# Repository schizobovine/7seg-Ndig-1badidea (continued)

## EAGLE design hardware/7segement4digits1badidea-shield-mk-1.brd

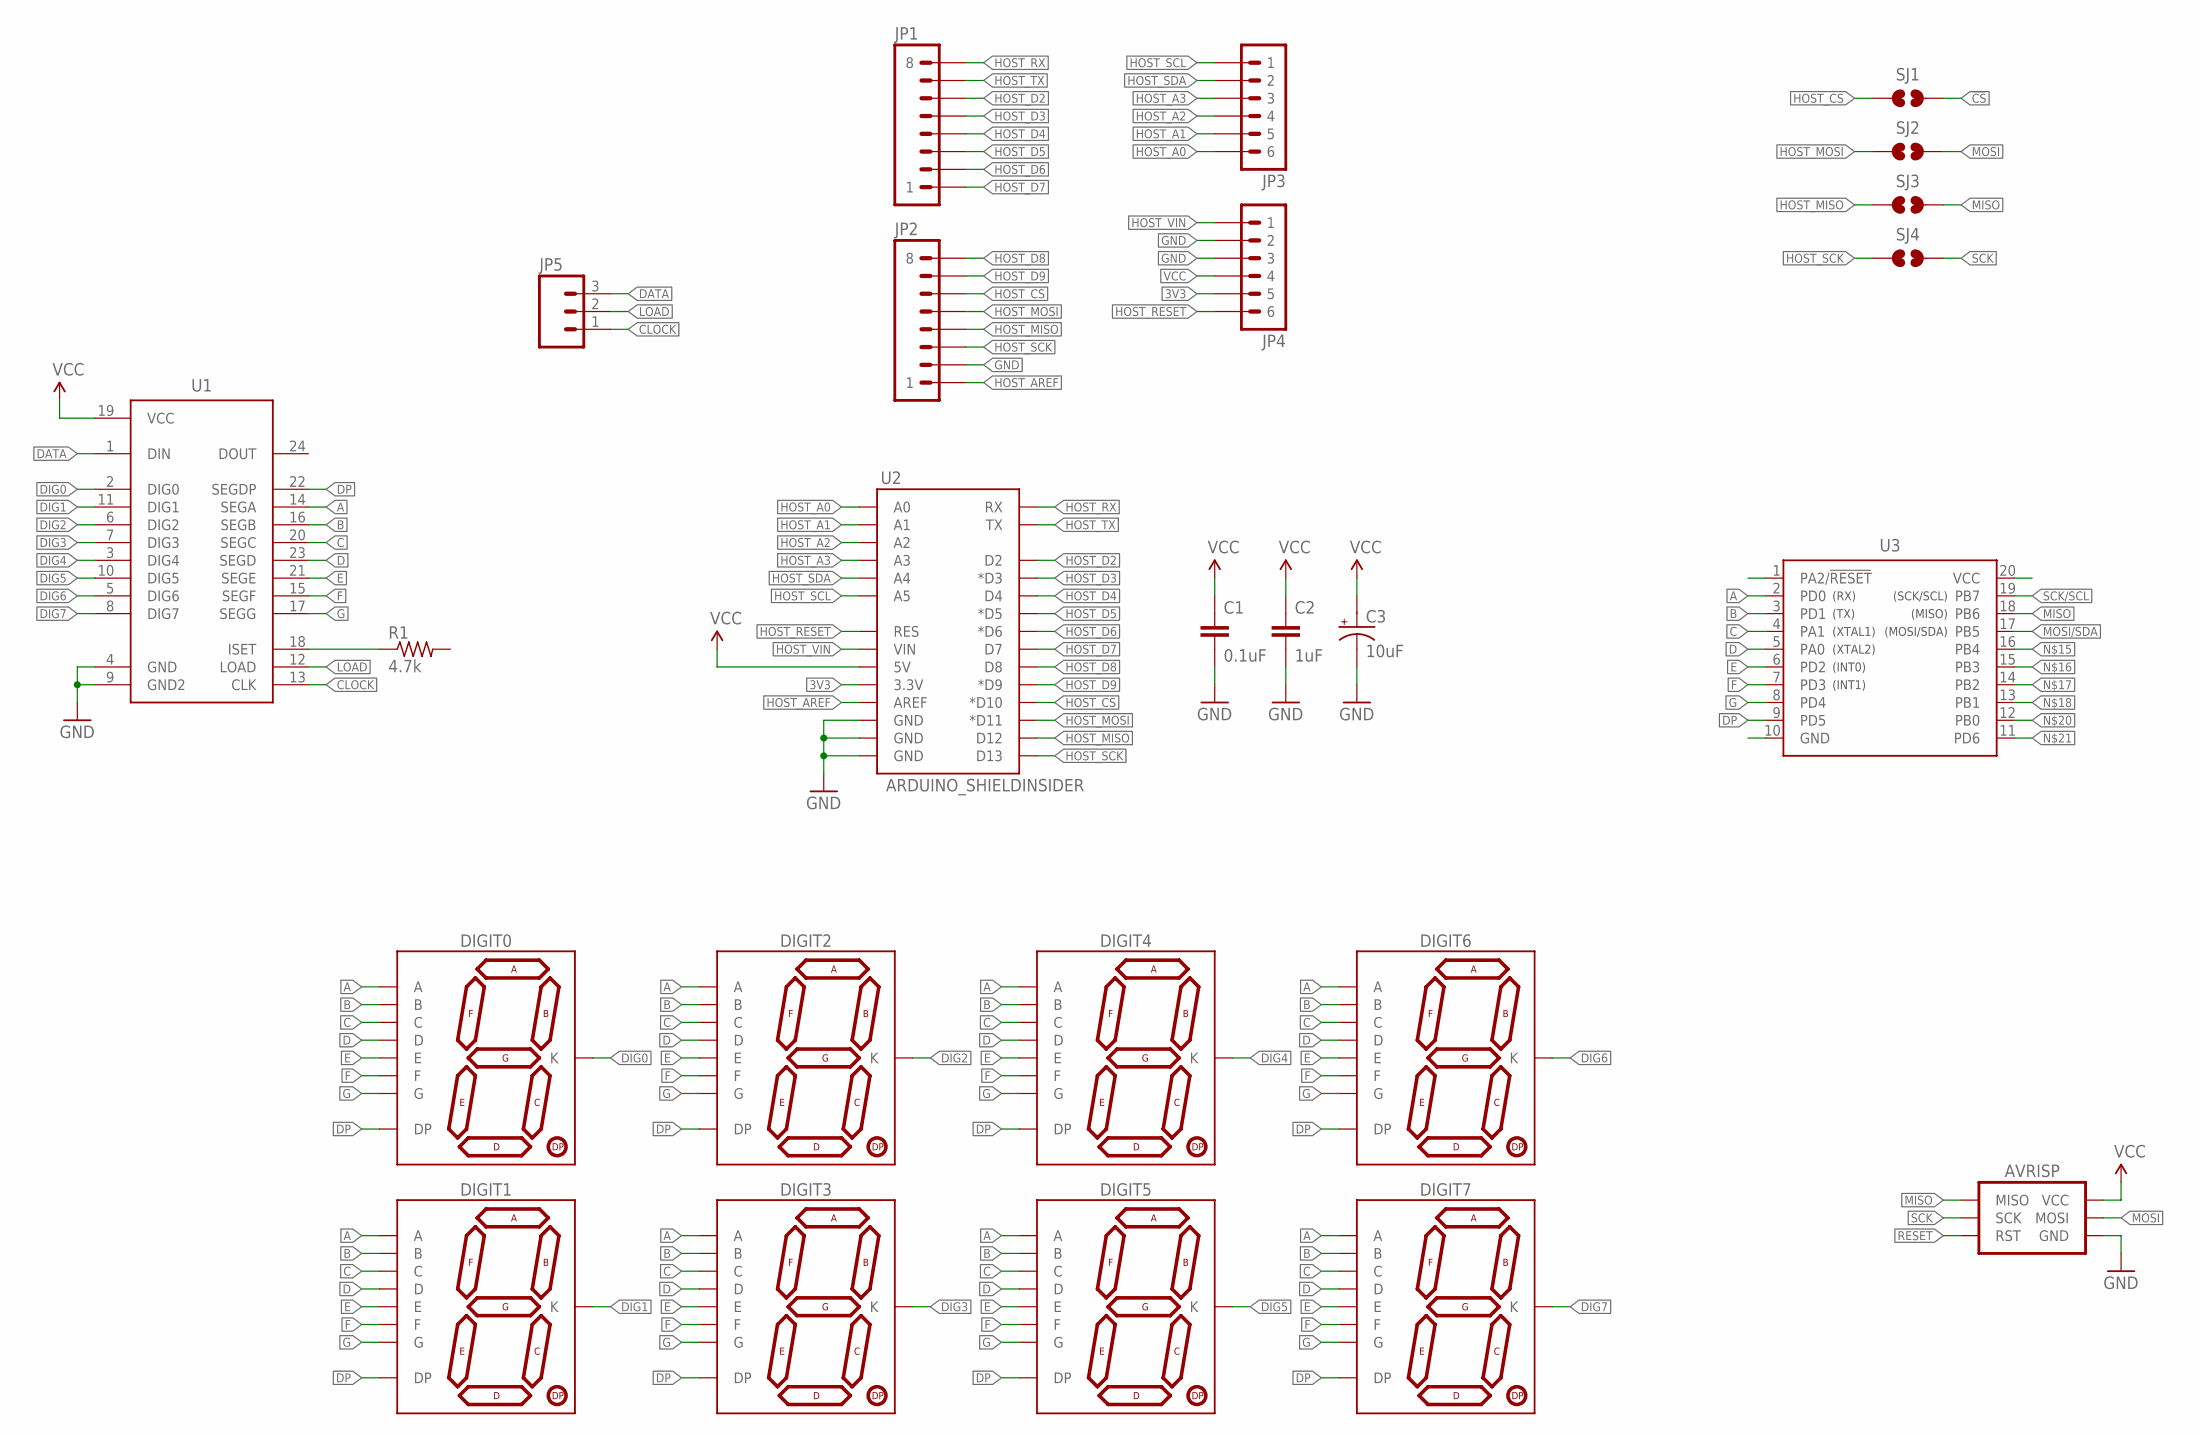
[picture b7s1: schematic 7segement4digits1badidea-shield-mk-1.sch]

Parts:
AVRISP: AVR_SPI_PRG_6PTH; 2X3
C1: 0.1uF; C025-024X044
C2: 1uF; C025-024X044
C3: 10uF; E2,5-5
DIGIT0, DIGIT1, DIGIT2, DIGIT3, DIGIT4, DIGIT5, DIGIT6, DIGIT7: 7SEG_1DIGPTH-10MM; 7SEG_1DIG_10MM
JP1, JP2: M081X08; 1X08
JP3, JP4: M06-NOBS-PTH; 1X06_NOLOCK_FUCKITALL
JP5: M03PTH; 1X03
R1: 4.7k; RESISTOR-AXIAL-PTH-6.35MM
SJ1, SJ2, SJ3, SJ4: JUMPER-PAD-2-NOYES_SILK; PAD-JUMPER-2-NO_YES_SILK
U1: MAX7219DIP; DIL24
U2: ARDUINO_SHIELDINSIDER; ARDUINO_SHIELD_NOOUTLINE_INSIDE
U3: ATTINY2313ADIP; DIL20

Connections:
3V3: JP4.5, U2.3.3V
!CS: SJ1.2
A: DIGIT0.10 (A), DIGIT1.10 (A), DIGIT2.10 (A), DIGIT3.10 (A), DIGIT4.10 (A), DIGIT5.10 (A), DIGIT6.10 (A), DIGIT7.10 (A), U1.14 (SEGA), U3.2 (PD0)
B: DIGIT0.9 (B), DIGIT1.9 (B), DIGIT2.9 (B), DIGIT3.9 (B), DIGIT4.9 (B), DIGIT5.9 (B), DIGIT6.9 (B), DIGIT7.9 (B), U1.16 (SEGB), U3.3 (PD1)
C: DIGIT0.8 (C), DIGIT1.8 (C), DIGIT2.8 (C), DIGIT3.8 (C), DIGIT4.8 (C), DIGIT5.8 (C), DIGIT6.8 (C), DIGIT7.8 (C), U1.20 (SEGC), U3.4 (PA1)
CLOCK: JP5.1, U1.13 (CLK)
D: DIGIT0.5 (D), DIGIT1.5 (D), DIGIT2.5 (D), DIGIT3.5 (D), DIGIT4.5 (D), DIGIT5.5 (D), DIGIT6.5 (D), DIGIT7.5 (D), U1.23 (SEGD), U3.5 (PA0)
DATA: JP5.3, U1.1 (DIN)
DIG0: DIGIT0.1 (K), DIGIT0.6 (K), U1.2 (DIG0)
DIG1: DIGIT1.1 (K), DIGIT1.6 (K), U1.11 (DIG1)
DIG2: DIGIT2.1 (K), DIGIT2.6 (K), U1.6 (DIG2)
DIG3: DIGIT3.1 (K), DIGIT3.6 (K), U1.7 (DIG3)
DIG4: DIGIT4.1 (K), DIGIT4.6 (K), U1.3 (DIG4)
DIG5: DIGIT5.1 (K), DIGIT5.6 (K), U1.10 (DIG5)
DIG6: DIGIT6.1 (K), DIGIT6.6 (K), U1.5 (DIG6)
DIG7: DIGIT7.1 (K), DIGIT7.6 (K), U1.8 (DIG7)
DP: DIGIT0.7 (DP), DIGIT1.7 (DP), DIGIT2.7 (DP), DIGIT3.7 (DP), DIGIT4.7 (DP), DIGIT5.7 (DP), DIGIT6.7 (DP), DIGIT7.7 (DP), U1.22 (SEGDP), U3.9 (PD5)
E: DIGIT0.4 (E), DIGIT1.4 (E), DIGIT2.4 (E), DIGIT3.4 (E), DIGIT4.4 (E), DIGIT5.4 (E), DIGIT6.4 (E), DIGIT7.4 (E), U1.21 (SEGE), U3.6 (PD2)
F: DIGIT0.2 (F), DIGIT1.2 (F), DIGIT2.2 (F), DIGIT3.2 (F), DIGIT4.2 (F), DIGIT5.2 (F), DIGIT6.2 (F), DIGIT7.2 (F), U1.15 (SEGF), U3.7 (PD3)
G: DIGIT0.3 (G), DIGIT1.3 (G), DIGIT2.3 (G), DIGIT3.3 (G), DIGIT4.3 (G), DIGIT5.3 (G), DIGIT6.3 (G), DIGIT7.3 (G), U1.17 (SEGG), U3.8 (PD4)
GND: AVRISP.6 (GND), C1.2, C2.2, C3.-, JP2.2, JP4.2, JP4.3, U1.4 (GND), U1.9 (GND2), U2.GND@0 (GND), U2.GND@1 (GND), U2.GND@2 (GND)
HOST_A0: JP3.6, U2.A0
HOST_A1: JP3.5, U2.A1
HOST_A2: JP3.4, U2.A2
HOST_A3: JP3.3, U2.A3
HOST_AREF: JP2.1, U2.AREF
HOST_CS: JP2.6, SJ1.1, U2.D10 (*D10)
HOST_D2: JP1.6, U2.D2
HOST_D3: JP1.5, U2.D3 (*D3)
HOST_D4: JP1.4, U2.D4
HOST_D5: JP1.3, U2.D5 (*D5)
HOST_D6: JP1.2, U2.D6 (*D6)
HOST_D7: JP1.1, U2.D7
HOST_D8: JP2.8, U2.D8
HOST_D9: JP2.7, U2.D9 (*D9)
HOST_MISO: JP2.4, SJ3.1, U2.D12
HOST_MOSI: JP2.5, SJ2.1, U2.D11 (*D11)
HOST_RESET: JP4.6, U2.RES
HOST_RX: JP1.8, U2.RX
HOST_SCK: JP2.3, SJ4.1, U2.D13
HOST_SCL: JP3.1, U2.A5
HOST_SDA: JP3.2, U2.A4
HOST_TX: JP1.7, U2.TX
HOST_VIN: JP4.1, U2.VIN
LOAD: JP5.2, U1.12 (LOAD)
MISO: AVRISP.1 (MISO), SJ3.2, U3.18 (PB6)
MOSI: AVRISP.4 (MOSI), SJ2.2
MOSI/SDA: U3.17 (PB5)
unnamed: R1.P$1 (1), U1.18 (ISET)
RESET: AVRISP.5 (RST)
SCK: AVRISP.3 (SCK), SJ4.2
SCK/SCL: U3.19 (PB7)
VCC: AVRISP.2 (VCC), C1.1, C2.1, C3.+, JP4.4, U1.19 (VCC), U2.5V

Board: 2 copper layers, 25 parts (0 on the bottom side), 49 nets, no tracks yet.
